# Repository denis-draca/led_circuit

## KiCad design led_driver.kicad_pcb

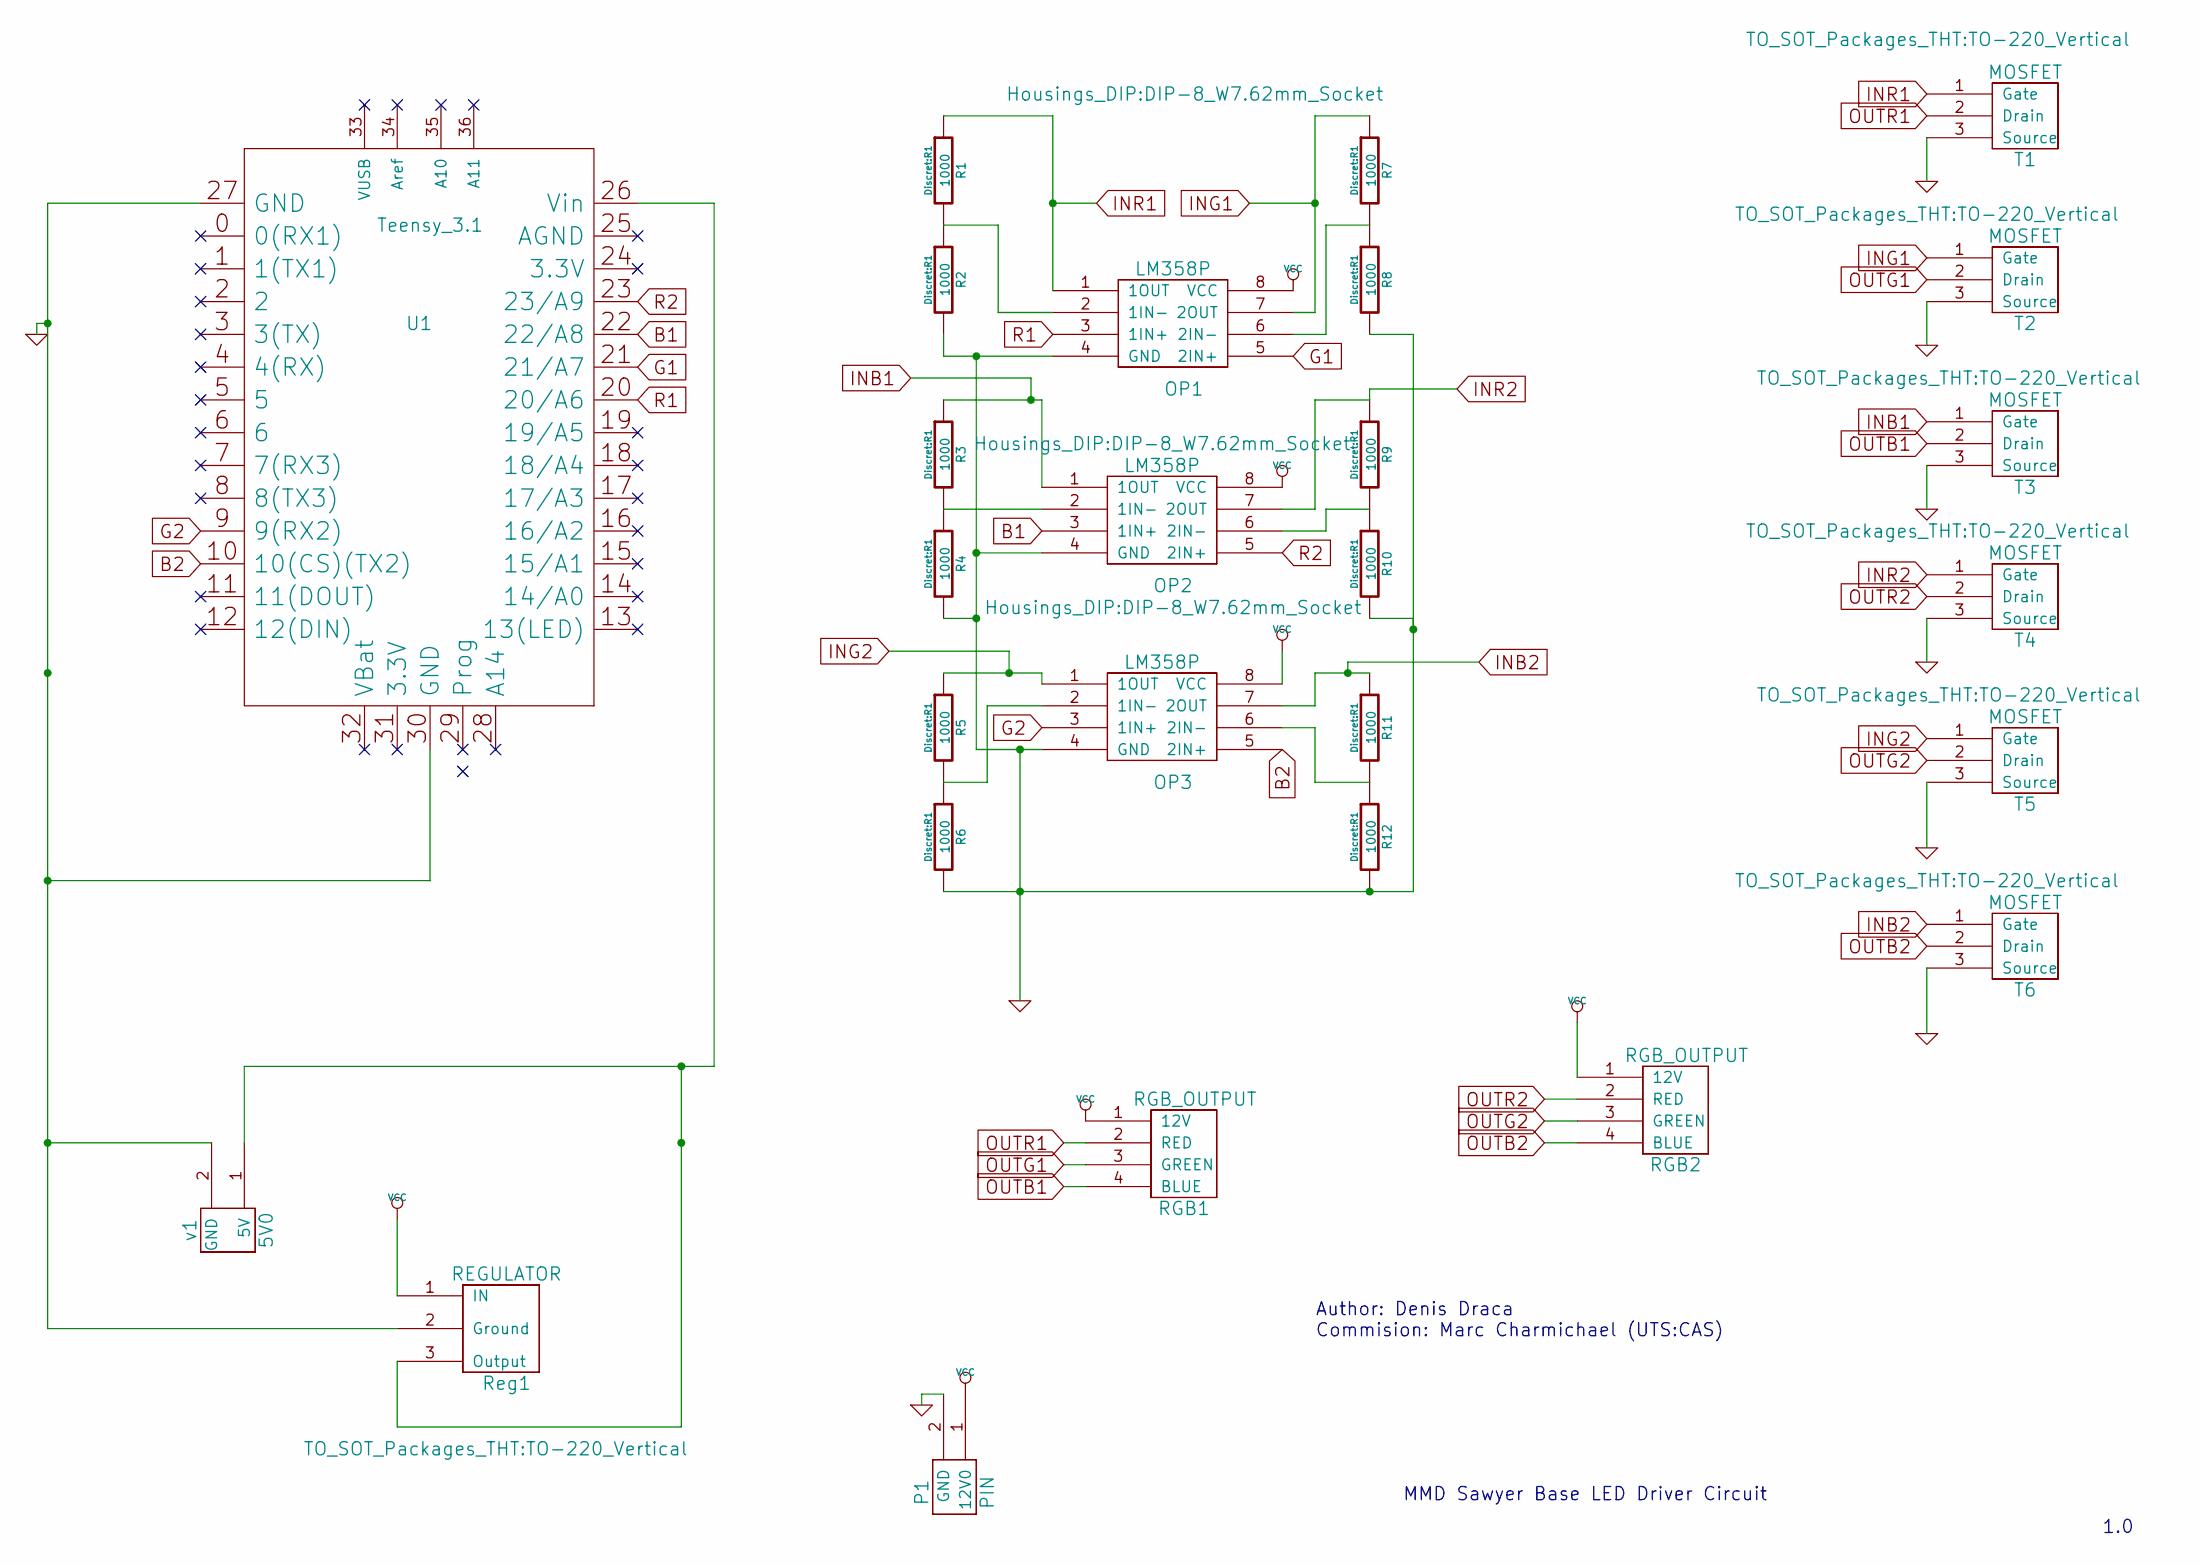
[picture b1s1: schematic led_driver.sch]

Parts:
OP1, OP2, OP3: LM358P; DIP-8_W7.62mm_Socket
P1: PIN; BARREL_JACK
R1, R2, R3, R4, R5, R6, R7, R8, R9, R10, R11, R12: 1000; R1
RGB1, RGB2: RGB_OUTPUT; rgbOUT
Reg1: REGULATOR; TO-220_Vertical
T1, T2, T3, T4, T5, T6: MOSFET; TO-220_Vertical
U1: Teensy_3.1; Teensy-3.1
v1: 5V0; 5vIN

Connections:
B1: OP2.3 (1IN+), U1.22 (22/A8)
B2: OP3.5 (2IN+), U1.10 (10(CS)(TX2))
G1: OP1.5 (2IN+), U1.21 (21/A7)
G2: OP3.3 (1IN+), U1.9 (9(RX2))
GND: OP1.4 (GND), OP2.4 (GND), OP3.4 (GND), P1.2 (GND), R2.2, R4.2, R6.2, R8.2, R10.2, R12.2, Reg1.2 (Ground), T1.3 (Source), T2.3 (Source), T3.3 (Source), T4.3 (Source), T5.3 (Source), T6.3 (Source), U1.27 (GND), U1.30 (GND), v1.2 (GND)
INB1: OP2.1 (1OUT), R3.1, T3.1 (Gate)
INB2: OP3.7 (2OUT), R11.1, T6.1 (Gate)
ING1: OP1.7 (2OUT), R7.1, T2.1 (Gate)
ING2: OP3.1 (1OUT), R5.1, T5.1 (Gate)
INR1: OP1.1 (1OUT), R1.1, T1.1 (Gate)
INR2: OP2.7 (2OUT), R9.1, T4.1 (Gate)
unnamed: OP1.2 (1IN-), R1.2, R2.1
unnamed: OP1.6 (2IN-), R7.2, R8.1
unnamed: OP2.2 (1IN-), R3.2, R4.1
unnamed: OP2.6 (2IN-), R9.2, R10.1
unnamed: OP3.2 (1IN-), R5.2, R6.1
unnamed: OP3.6 (2IN-), R11.2, R12.1
unnamed: Reg1.3 (Output), U1.26 (Vin), v1.1 (5V)
OUTB1: RGB1.4 (BLUE), T3.2 (Drain)
OUTB2: RGB2.4 (BLUE), T6.2 (Drain)
OUTG1: RGB1.3 (GREEN), T2.2 (Drain)
OUTG2: RGB2.3 (GREEN), T5.2 (Drain)
OUTR1: RGB1.2 (RED), T1.2 (Drain)
OUTR2: RGB2.2 (RED), T4.2 (Drain)
R1: OP1.3 (1IN+), U1.20 (20/A6)
R2: OP2.5 (2IN+), U1.23 (23/A9)
VCC: OP1.8 (VCC), OP2.8 (VCC), OP3.8 (VCC), P1.1 (12V0), RGB1.1 (12V), RGB2.1 (12V), Reg1.1 (IN)

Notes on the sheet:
MMD Sawyer Base LED Driver Circuit
Author: Denis Draca Commision: Marc Charmichael (UTS:CAS)
1.0

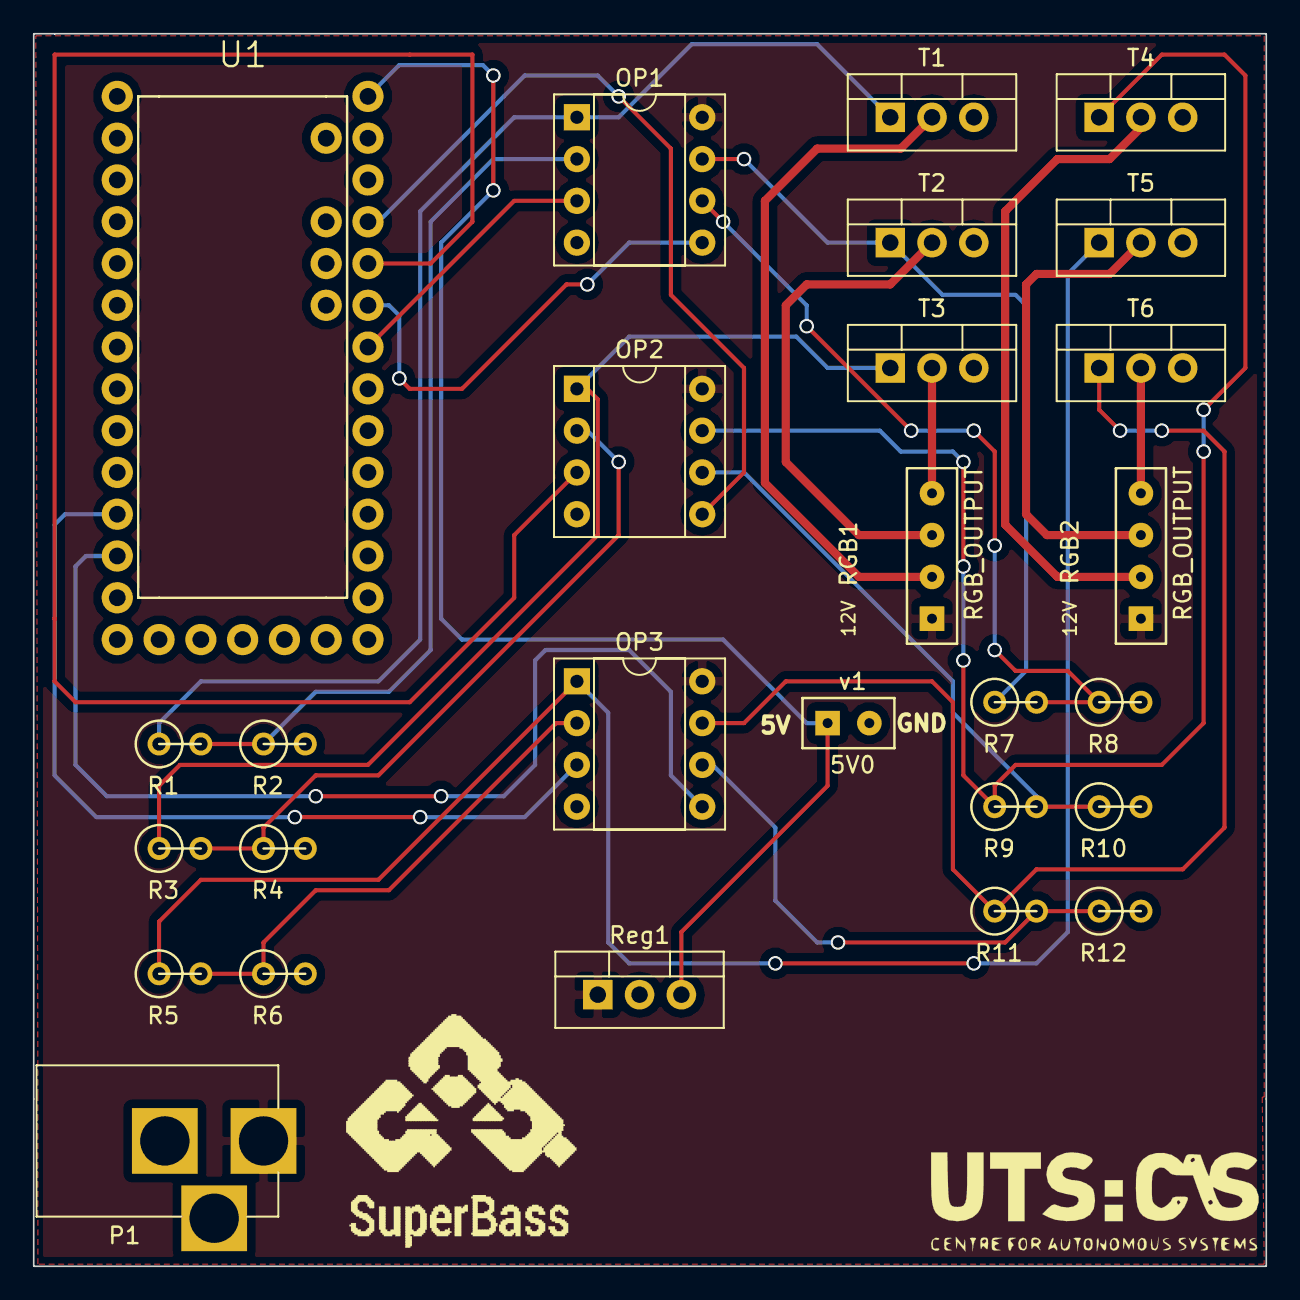
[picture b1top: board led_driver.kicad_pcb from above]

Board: 2 copper layers, 74.9 x 74.9 mm, 28 parts (0 on the bottom side), 27 nets.

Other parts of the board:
pnglogo: logov2

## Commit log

2017-06-10 added schematic print. Produced GERBER files (manufacturing drawings). Slight rewiring to give larger passage ways for higher current flow
2017-06-12 added DC jack, added 3d models for the RGB connectors and opamps
2017-06-12 removed big file
2017-06-13 fixed DC barrel jack slot issue
2017-06-25 fixed hole size for headers
